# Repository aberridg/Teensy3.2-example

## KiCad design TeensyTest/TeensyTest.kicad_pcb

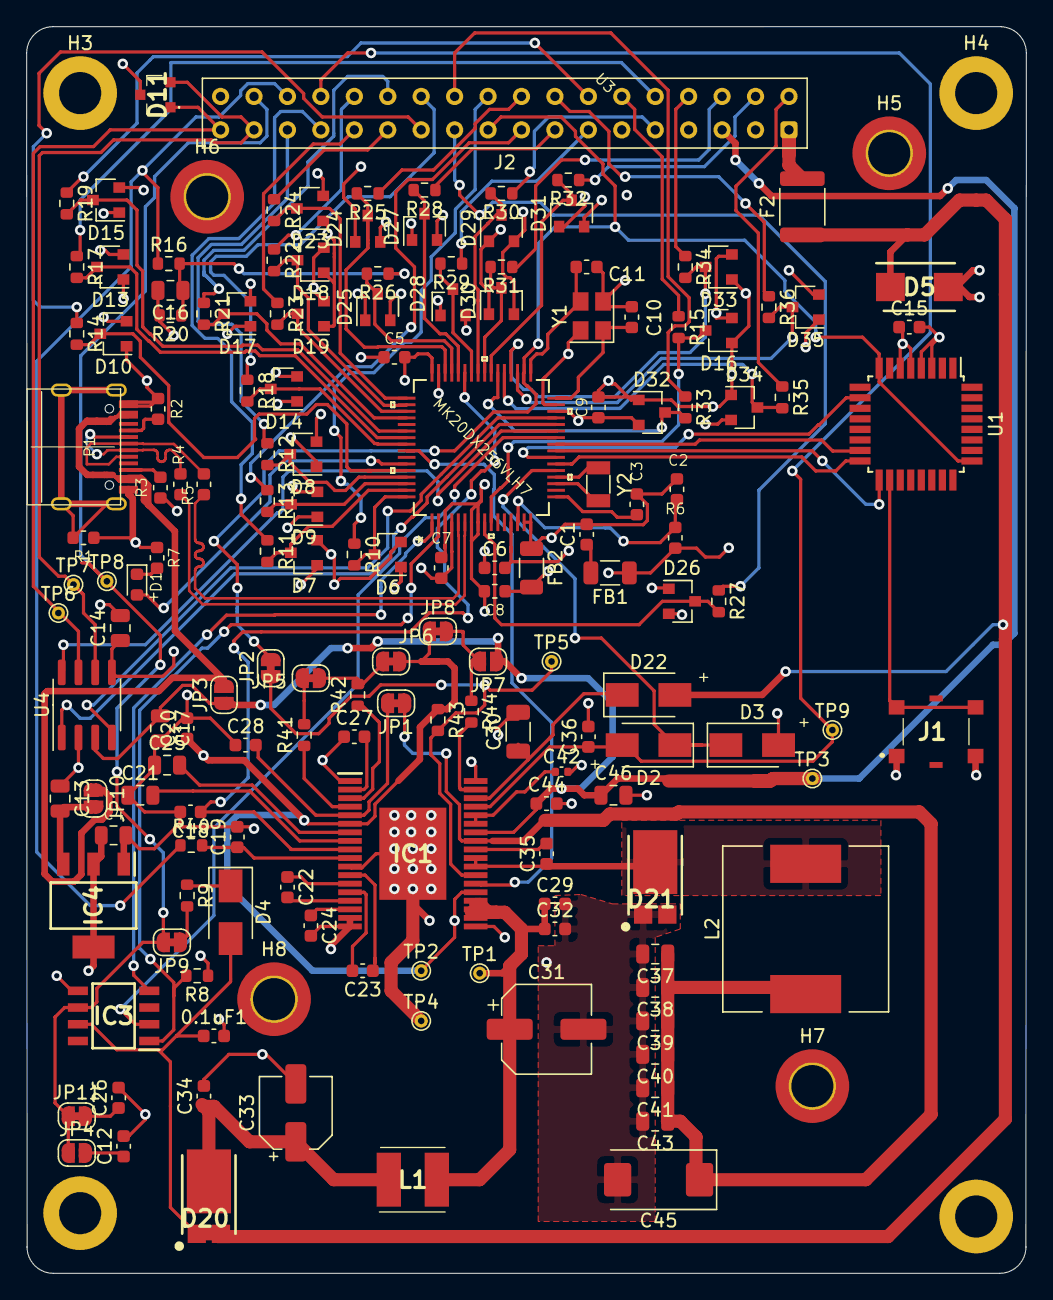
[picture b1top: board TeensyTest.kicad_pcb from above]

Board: 4 copper layers, 75.9 x 94.7 mm, 166 parts (0 on the bottom side), 123 nets.

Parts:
0.1uF1: C; C_0603_1608Metric
C1: 2.2uF; C_0603_1608Metric
C2, C3, C5, C6, C7, C8, C9, C15: 0.1uF; C_0603_1608Metric
C4, C13: 10uF; C_0805_2012Metric
C10, C11: 10pF; C_0603_1608Metric
C12: 220pF; C_0603_1608Metric
C14, C16, C17: 0.1uF; C_0805_2012Metric
C18: 10nF/50V; C_0603_1608Metric
C19, C29, C32, C34: 0.1uF/50V; C_0603_1608Metric
C20, C36: 1uF/10V; C_0603_1608Metric
C21, C25: 4.7uF/25V; C_0805_2012Metric
C22, C23, C28: 0.1uF/16V; C_0603_1608Metric
C24: 0.22uF/25V; C_0603_1608Metric
C26: 1nF; C_0603_1608Metric
C27: 1n/10V; C_0603_1608Metric
C30: 470nF/50V; C_1206_3216Metric
C31: 10uF/50V; CP_Elec_6.3x5.4
C33: 10uF/50V; CP_Elec_5x5.3
C35: 0.1uF/10V; C_0603_1608Metric
C37, C38, C39, C40, C41, C43: 4.7uF/16V; C_0805_2012Metric
C42: 220nF; C_0402_1005Metric
C44: 10uF/10V; C_0603_1608Metric
C45: 47uF/16V; CP_EIA-7343-31_Kemet-D
C46: 1uF/10V; C_0805_2012Metric
D1: LED_Small; LED_0603_1608Metric
D2, D3, D4, D22: D; D_SMA
D5: SMBJ33A; DIOM5436X244N
D6, D7, D8, D9, D10, D13, D14, D15, D16, D17, D18, D19, D23, D24, D25, D26, D27, D28, D29, D30, D31, D32, D33, D34, D35: BAS40-04; SOT-23
D11: SM24CANB-02HTG; SM24CANB02HTG
D20, D21: SBR12U100P5-13; POWERDI5
F2: Fuse; Fuse_1812_4532Metric
FB1, FB2: Ferrite_Bead_Small; R_1206_3216Metric
H1, H2, H3, H4: MountingHole; MountingHole_3.2mm_M3_DIN965_Pad
H5, H6, H7, H8: MountingHole_Pad; MountingHole_3.2mm_M3_DIN965_Pad_TopBottom
IC1: TLE73683EXUMA2; SOP65P1030X255-37N
IC3: TLIN2029DRQ1; SOIC127P600X175-8N
IC4: LM1117MPX-3.3_NOPB; SOT230P700X180-4N
J1: 431151015826
J2: Conn_02x18_Odd_Even; Samtec_HLE-118-02-xx-DV-TE_2x18_P2.54mm_Horizontal
JP1: SolderJumper_2_Bridged!!!; SolderJumper-2_P1.3mm_Bridged_RoundedPad1.0x1.5mm
JP2, JP5, JP6, JP8: SolderJumper_2_Bridged; SolderJumper-2_P1.3mm_Bridged_RoundedPad1.0x1.5mm
JP3, JP10: SolderJumper_2_Bridged; SolderJumper-2_P1.3mm_Open_RoundedPad1.0x1.5mm
JP4: Jumper_2_Open; SolderJumper-2_P1.3mm_Open_RoundedPad1.0x1.5mm
JP7: SolderJumper_2_Open; SolderJumper-2_P1.3mm_Open_RoundedPad1.0x1.5mm
JP9, JP11: Jumper_2_Closed; SolderJumper-2_P1.3mm_Bridged_RoundedPad1.0x1.5mm
L1: 10 μH/2.1 A; LQH5BPN100M38L
L2: 33 μH/2.1 A; L_12x12mm_H6mm
P1: USB_C_Plug_USB2.0; TYPE-C-31-M-12
R1: 1M; R_0603_1608Metric
R2, R3: 5.1k; R_0603_1608Metric
R4, R5: 33R; R_0603_1608Metric
R6, R7: 470R; R_0603_1608Metric
R8: 4K7; R_0603_1608Metric
R9: 1K; R_0603_1608Metric
R10, R11, R12, R13, R14, R15, R17, R18, R19, R21, R22, R23, R24, R25, R26, R27, R28, R29, R30, R31, R32, R33, R34, R35, R36: 4.7K; R_0603_1608Metric
R16: 180K; R_0603_1608Metric
R20: 68K; R_0603_1608Metric
R40, R41, R42, R43, R44: 10K; R_0603_1608Metric
TP1, TP2, TP3, TP4, TP5, TP6, TP7, TP8, TP9: TestPoint; TestPoint_THTPad_D1.0mm_Drill0.5mm
U1: MKL02Z32VFG4; TQFP-32_7x7mm_P0.8mm
U3: MK20DX256VLH7
U4: MCP2562-E-SN; SOIC-8_3.9x4.9mm_P1.27mm
Y1: Crystal_GND24; Crystal_SMD_3225-4Pin_3.2x2.5mm
Y2: Crystal; Crystal_SMD_3215-2Pin_3.2x1.5mm

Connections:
+3V3: C4.2, C5.2, C6.2, C7.2, C8.2, C9.2, C14.1, C15.2, C20.1, D3.2, D6.2, D7.2, D8.2, D9.2, D10.2, D13.2, D14.2, D15.2, D16.2, D17.2, D18.2, D19.2, D23.2, D24.2, D25.2, D26.2, D27.2, D28.2, D29.2, D30.2, D31.2, D32.2, D33.2, D34.2, D35.2, FB1.1, IC1.6, IC1.23, IC4.2, IC4.4, J2.3, JP6.1, JP8.1, R6.2, R8.1, R43.1, TP2.1, U1.3, U1.4, U3.3, U3.7, U3.8, U3.13, U3.30, U3.48, U4.5
+5V: C17.1, C44.1, C46.1, IC1.30, J2.5, JP3.1, JP7.1, TP3.1, U4.3
+12V: F2.2, J2.1
/2: IC1.24, U3.57
/5: J2.20, R10.1
/6: J2.31, R12.1
/8: J2.23, R14.1
/9: J2.18, R25.1
/15_A1: C18.1, IC1.9, U3.43
/20_A6: J2.17, R13.1
/21_A7: J2.29, R11.1
/22_A8: J2.15, R28.1
/23_A9: C16.1, R16.2, R20.1, R26.1
/24: U3.27, U4.8
/26: IC3.1, R8.2, U3.2
/27: J2.14, R19.1
/29: J2.10, R17.1
/30: J2.24, R18.1
/31: IC3.4, U3.1
/33: IC3.2, U3.26
/A10: J2.21, R27.1
/A10_1: D26.3, R27.2, U3.9
/A11: J2.12, R15.1
/A11_1: D16.3, R15.2, U3.10
/CANH: D11.1, J2.35, TP6.1, U4.7
/CANL: D11.2, J2.33, TP7.1, U4.6
/CC1: P1.A5, R2.2
/CC2: P1.B5, R3.2
/CRX: U3.29, U4.4
/CTX: U3.28, U4.1
/D0: J2.4, R32.1
/D1: J2.6, R31.1
/D7: D1.2, U3.59
/D10: J2.25, R24.1
/D11: J2.27, R23.1
/D12: J2.26, R21.1
/D13: J2.28, R22.1
/D16: J2.16, R36.1
/D17: J2.8, R34.1
/D18: J2.22, R33.1
/D19: J2.2, R35.1
/D25: J2.13, R29.1
/D32: J2.9, R30.1
/D+: P1.A6, P1.B6, R5.2
/D-: P1.A7, P1.B7, R4.2
/D_N: R4.1, U3.6
/D_P: R5.1, U3.5
/IGN: J2.32, R16.1, R40.1
/InputProtection/1: D6.3, R10.2, U3.64
/LIN: IC3.6, J2.34, JP4.1, JP9.2, JP11.1, TP8.1
/Q_STBY: C36.1, D2.2, IC1.33, J2.30, TP9.1
/TLE73683EXUMA2/BUCK: C37.1, C38.1, C39.1, C40.1, C41.1, C43.1, C45.1, IC1.29, JP1.1, L2.1
/TLE73683EXUMA2/DRV_EXT: C42.1, IC1.31, IC1.32
/TLE73683EXUMA2/IN_LDO2: C28.2, IC1.5, JP1.2
/TLE73683EXUMA2/SW_1: C35.1, D21.3, IC1.26, IC1.27, L2.2
/TLE73683EXUMA2/WDO: IC1.25, JP2.1, R43.2, TP5.1
/sheet606C2E9F/1: D9.3, R13.2, U3.62
/sheet606D7D50/1: D10.3, R14.2, U3.60
/sheet606F9353/1: D13.3, R17.2, U3.55
/sheet606F9354/1: D14.3, R18.2, U3.56
/sheet606F9355/1: D15.3, R19.2, U3.54
/sheet606FF68B/1: D17.3, R21.2, U3.52
/sheet606FF68C/1: D18.3, R22.2, U3.50
/sheet606FF68D/1: D19.3, R23.2, U3.51
/sheet606FF68E/1: D23.3, R24.2, U3.49
/sheet6068C209/1: D8.3, R12.2, U3.61
/sheet60685D3E/1: D7.3, R11.2, U3.63
/sheet60705A00/1: D25.3, R26.2, U3.45
/sheet60705A02/1: D27.3, R28.2, U3.44
/sheet60705A03/1: D28.3, R29.2, U3.42
/sheet607059FF/1: D24.3, R25.2, U3.46
/sheet6079145B/1: D29.3, R30.2, U3.41
/sheet6079145C/1: D30.3, R31.2, U3.40
/sheet6079145D/1: D31.3, R32.2, U3.39
/sheet6079145E/1: D32.3, R33.2, U3.38
/sheet6079145F/1: D33.3, R34.2, U3.36
/sheet60791460/1: D34.3, R35.2, U3.37
/sheet60791461/1: D35.3, R36.2, U3.35
GND: 0.1uF1.2, C4.1, C5.1, C6.1, C7.1, C8.1, C9.1, C12.2, C13.1, C14.2, C15.1, C16.2, C17.2, C18.2, C19.2, C20.2, C21.1, C24.2, C25.1, C26.2, C27.1, C28.1, C29.2, C30.2, C31.2, C32.2, C33.2, C34.2, C36.2, C37.2, C38.2, C39.2, C40.2, C41.2, C42.2, C43.2, C44.2, C45.2, C46.2, D5.2, D6.1, D7.1, D8.1, D9.1, D10.1, D11.3, D13.1, D14.1, D15.1, D16.1, D17.1, D18.1, D19.1, D21.1, D21.2, D23.1, D24.1, D25.1, D26.1, D27.1, D28.1, D29.1, D30.1, D31.1, D32.1, D33.1, D34.1, D35.1, FB2.2, H5.1, H6.1, H7.1, H8.1, IC1.1, IC1.11, IC1.17, IC1.18, IC1.19, IC1.36, IC1.37, IC3.5, IC4.1, J1.1, J1.3, J2.7, J2.36, P1.A1, P1.A12, P1.B1, P1.B12, R1.1, R2.1, R3.1, R7.2, R20.2, TP4.1, U1.5, U1.6, U3.4, U3.47, U4.2
GND1: C10.2, C11.2, U3.31, Y1.2, Y1.4
unnamed: C1.1, FB1.2
unnamed: C1.2, C2.2, C3.1, FB2.1, U3.15, U3.16
unnamed: C2.1, R6.1, U3.14
unnamed: C3.2, U3.17
unnamed: C10.1, U3.32, Y1.1
unnamed: C11.1, U3.33, Y1.3
unnamed: C12.1, JP4.2
unnamed: C13.2, IC4.3, JP10.2
unnamed: C19.1, IC1.10, R40.2
unnamed: C21.2, IC1.8
unnamed: C22.1, IC1.13
unnamed: C22.2, IC1.15
unnamed: C23.1, IC1.12
unnamed: C23.2, IC1.14
unnamed: C24.1, IC1.16
unnamed: C25.2, IC1.7
unnamed: C26.1, JP11.2
unnamed: C27.2, IC1.2
unnamed: C29.1, C31.1, C32.1, IC1.20, IC1.21, IC1.22, L1.2, TP1.1
unnamed: C30.1, D22.1, IC1.34
unnamed: C33.1, C34.1, D20.3, L1.1
unnamed: C35.2, IC1.28
unnamed: D1.1, R7.1
unnamed: D2.1, D3.1, U3.21
unnamed: D4.1, R9.1
unnamed: IC1.3, R42.1
unnamed: IC1.4, R41.1
unnamed: IC1.35, R44.2
unnamed: J1.2, J1.4, U1.18
unnamed: JP5.1, R41.2
unnamed: JP5.2, JP6.2, R42.2
unnamed: JP7.2, JP8.2, R44.1
unnamed: JP9.1, R9.2
unnamed: P1.S1, R1.2
unnamed: U1.10, U3.23
unnamed: U1.15, U3.25
unnamed: U1.16, U3.22
unnamed: U1.17, U3.24
unnamed: U3.19, Y2.1
unnamed: U3.20, Y2.2
RESET_B: J2.19, JP2.2, U1.8, U1.25, U3.34
VBUS: JP3.2, JP10.1, P1.A4, P1.A9, P1.B4, P1.B9
VCC: 0.1uF1.1, D4.2, D5.1, D20.1, D20.2, D22.2, F2.1, IC3.7

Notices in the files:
parts and their libraries:
Copyright 2016 Accelerated Designs. All rights reserved.
